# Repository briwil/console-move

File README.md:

# Console on the Ableton Move

An 8-track tape recorder with OP-1/OP-XY-style editing, up to 8 instruments (drum machines and synths, including
ones from Schwung's catalog) and step sequencers, running as an app on an Ableton Move.

- **Install:** the one-line command on [consoleforthemove.com](https://consoleforthemove.com) (needs RNBO Move Takeover on the Move)
- **Releases and notes:** [Releases](https://github.com/briwil/console-move/releases)
- **How to use it:** [move/manual/Console-on-Move-Manual.pdf](move/manual/Console-on-Move-Manual.pdf)
- **How it works / notes:** [move/MOVE-NOTES.md](move/MOVE-NOTES.md)
- **Updating the Move:** Menu, SETTINGS, SOFTWARE UPDATE (see [move/UPDATE.md](move/UPDATE.md))

| Folder | What it holds |
|---|---|
| `move/` | The Move's screen and buttons, the updater, the build script, notes and manual |
| `pi-app/` | The app itself: audio engine, sound core (C), drum machines, sequencers, Schwung support, Ableton Link |
| `tools/` | The screen designer and the stand-in modules the Move app uses |

The libraries (synths, sound core, Link...) are compiled in the cloud by GitHub Actions
(`.github/workflows/move-libs.yml`) and downloaded by the updater.

*Originally this was a Raspberry Pi recorder; its history (including the KiCad control board) is in the git log.*

## Licence and third-party work

Console is free software under the GNU General Public License v3.0 ([LICENSE](LICENSE)). It bundles drum engines, effects and Schwung modules made by other people, each under its own licence; they are listed in [THIRD-PARTY-NOTICES.md](THIRD-PARTY-NOTICES.md). Those modules belong to their authors. If you made one and want it credited differently, relicensed or removed, please open an issue on this repository and it will be dealt with promptly.

"Erica Synths", "LXR" and "LXR-02" are trademarks of Erica Synths; "Ableton" and "Move" are trademarks of Ableton AG. Console is not affiliated with or endorsed by either company.

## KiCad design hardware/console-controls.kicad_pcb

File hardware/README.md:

# Control board (rev 0.1)

The next version, split into three boards with 16 step buttons and 6 more keys, is in
[v2/](v2/README.md).

Open `console-controls.kicad_pro` in KiCad 10. The project's footprint library,
`console.pretty`, has the PGA2350 and the Kailh Choc hotswap footprints, and
`fp-lib-table` loads it automatically.

- `console-controls.kicad_pcb` is the final routed board that was ordered from
  JLCPCB (0 DRC errors).
- `console-controls.kicad_sch` is the schematic with LCSC part numbers. If you
  edited the schematic yourself in KiCad, replace this copy with yours.
- `jlcpcb-order/` holds the BOM and CPL used for assembly, which places 40
  parts on the bottom side. The hotswap sockets were out of stock, so they're
  left off and get hand-soldered.

## Pin map (PGA2350)

| Function | Pins |
|---|---|
| Key matrix rows ROW0–ROW5 | GP2–GP7 |
| Key matrix columns COL0–COL5 | GP8–GP13 |
| Encoders ENC1–ENC11, A/B | GP14/15 … GP34/35, in order |
| Spare | GP0, GP1, GP36–GP46 |
| Reserved | GP47 (PSRAM chip select) |

- **Matrix:** 6×6, COL2ROW. Each diode's cathode (the bar) faces the row.
- **Keys:** SW1–SW16 are the 4×4 grid and SW17–SW24 are the track keys.
- **Encoder pushes:** the ENC1–ENC11 push switches are also in the matrix.
- **Buttons:** SW25 is BOOT and SW26 is RESET.

## Hand assembly after the boards arrive

1. Snap off the 5 mm edge rails.
2. Solder the 24 hotswap sockets on the back.
3. Solder the 11 EC11 encoders.
4. Solder the PGA2350, using 2.54 mm headers or soldering it directly.

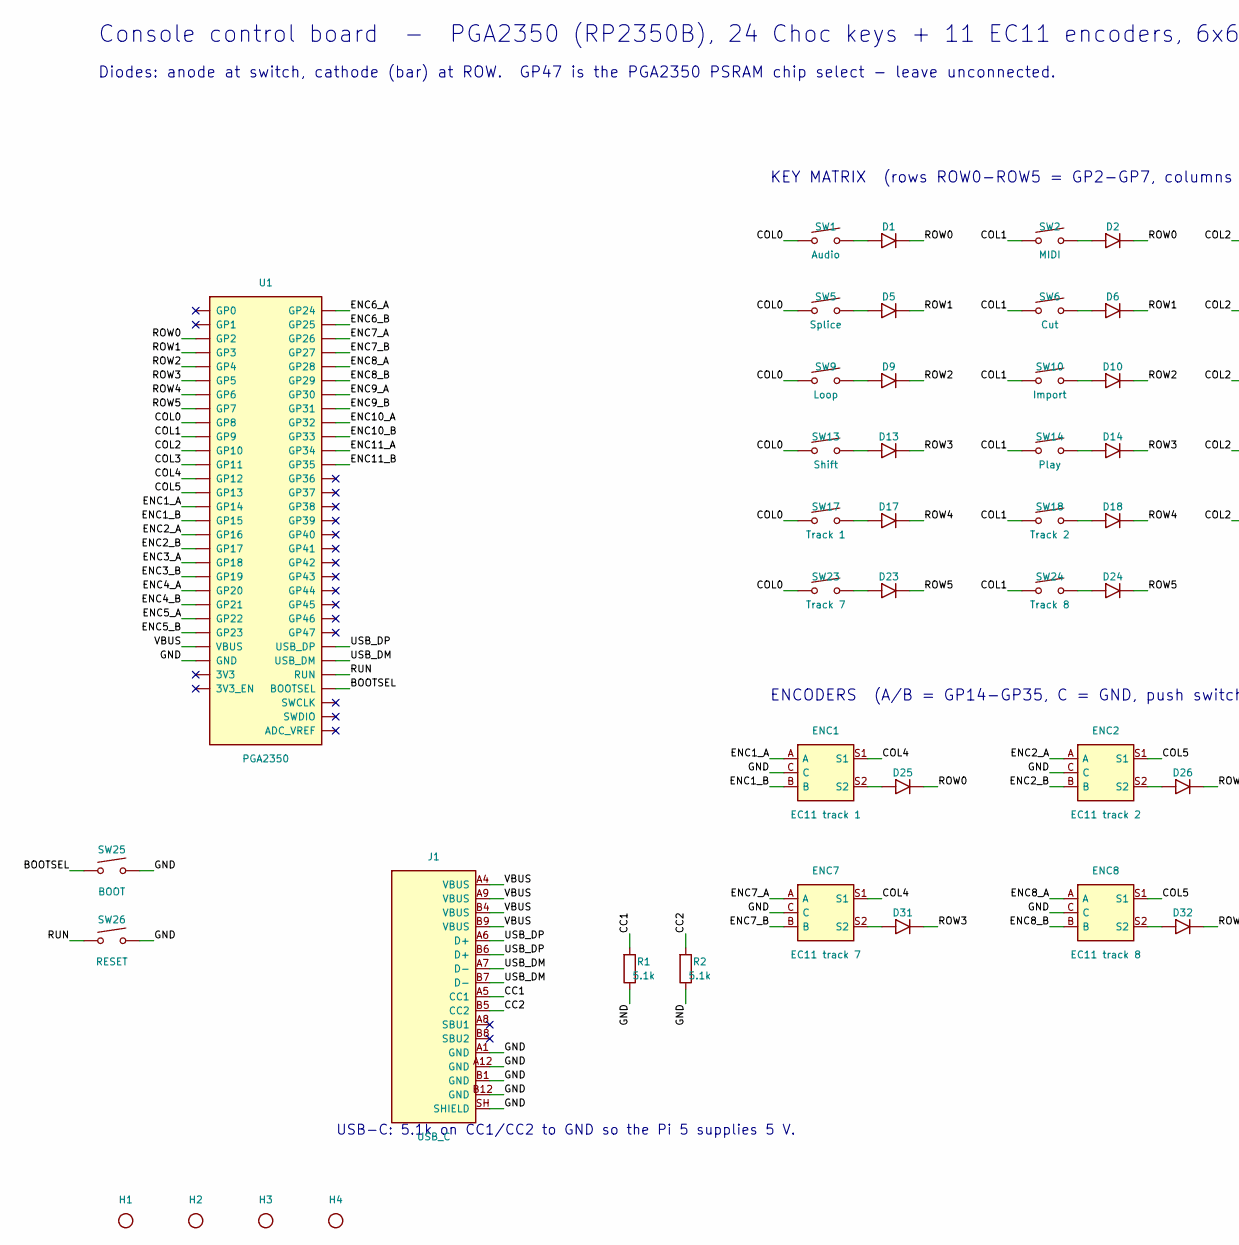
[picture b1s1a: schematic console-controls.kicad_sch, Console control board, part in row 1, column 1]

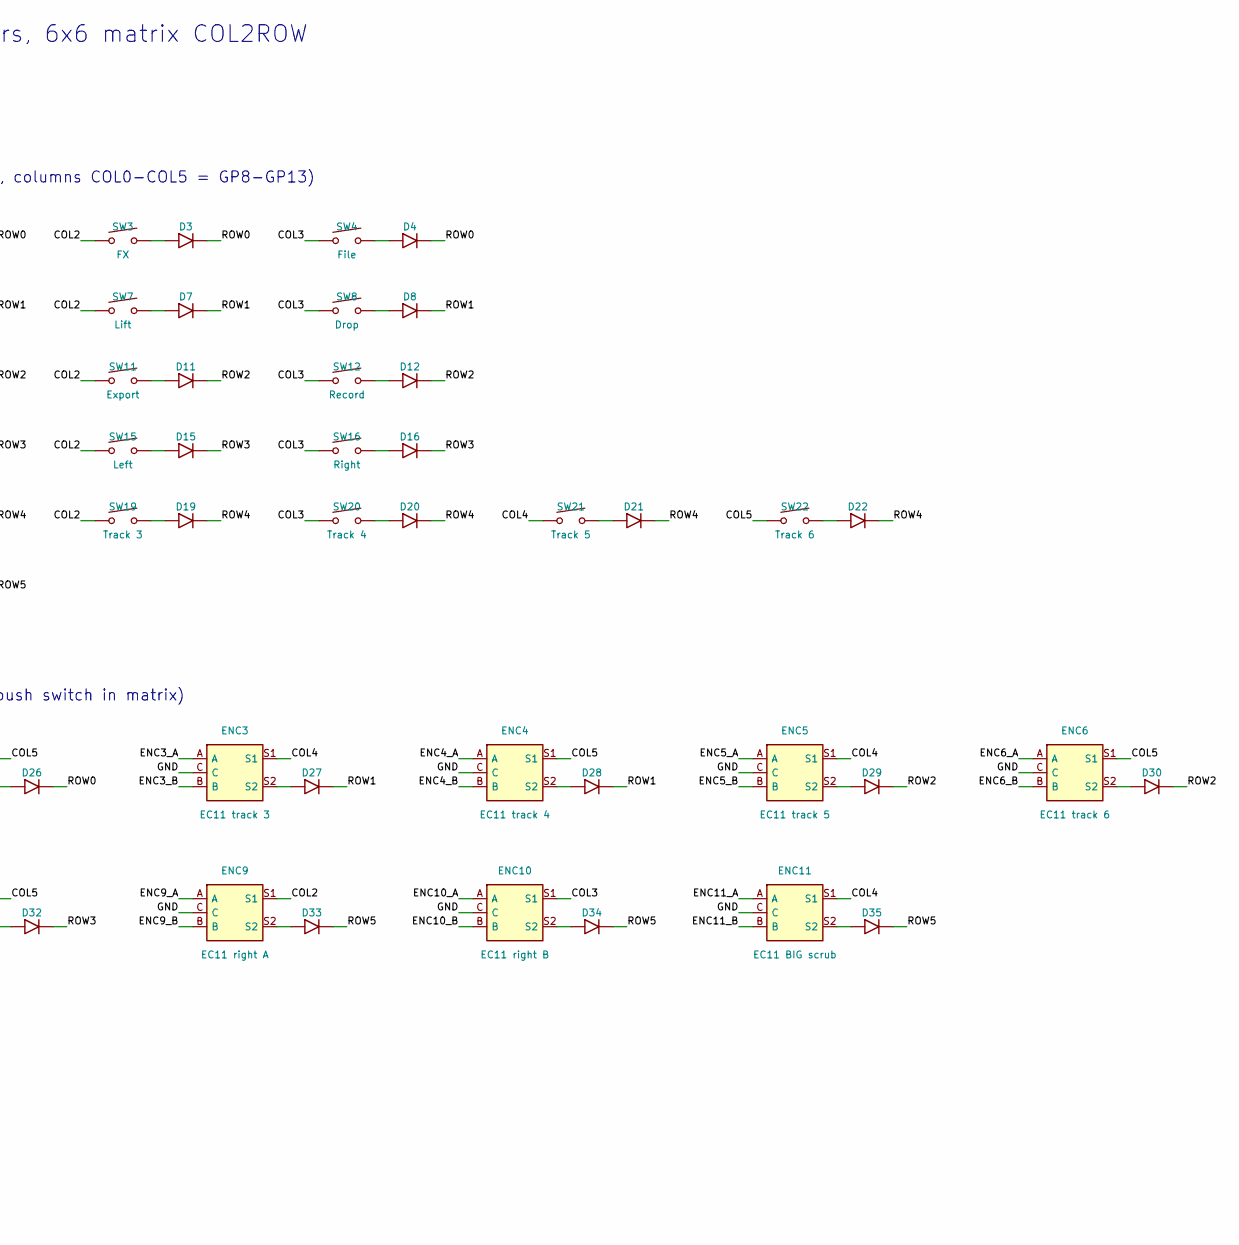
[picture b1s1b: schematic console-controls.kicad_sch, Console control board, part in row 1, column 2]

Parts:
D1, D2, D3, D4, D5, D6, D7, D8, D9, D10, D11, D12, D13, D14, D15, D16, D17, D18, D19, D20, D21, D22, D23, D24, D25, D26, D27, D28, D29, D30, D31, D32, D33, D34, D35: 1N4148W; D_SOD-123; LCSC C81598
ENC1: EC11 track 1; RotaryEncoder_Alps_EC11E-Switch_Vertical_H20mm
ENC2: EC11 track 2; RotaryEncoder_Alps_EC11E-Switch_Vertical_H20mm
ENC3: EC11 track 3; RotaryEncoder_Alps_EC11E-Switch_Vertical_H20mm
ENC4: EC11 track 4; RotaryEncoder_Alps_EC11E-Switch_Vertical_H20mm
ENC5: EC11 track 5; RotaryEncoder_Alps_EC11E-Switch_Vertical_H20mm
ENC6: EC11 track 6; RotaryEncoder_Alps_EC11E-Switch_Vertical_H20mm
ENC7: EC11 track 7; RotaryEncoder_Alps_EC11E-Switch_Vertical_H20mm
ENC8: EC11 track 8; RotaryEncoder_Alps_EC11E-Switch_Vertical_H20mm
ENC9: EC11 right A; RotaryEncoder_Alps_EC11E-Switch_Vertical_H20mm
ENC10: EC11 right B; RotaryEncoder_Alps_EC11E-Switch_Vertical_H20mm
ENC11: EC11 BIG scrub; RotaryEncoder_Alps_EC11E-Switch_Vertical_H20mm
H1, H2, H3, H4: MountingHole; MountingHole_3.2mm_M3
J1: USB_C; USB_C_Receptacle_HRO_TYPE-C-31-M-12; LCSC C165948
R1, R2: 5.1k; R_0603_1608Metric; LCSC C23186
SW1: Audio; SW_Kailh_Choc_V1_Hotswap; LCSC C5333465
SW2: MIDI; SW_Kailh_Choc_V1_Hotswap; LCSC C5333465
SW3: FX; SW_Kailh_Choc_V1_Hotswap; LCSC C5333465
SW4: File; SW_Kailh_Choc_V1_Hotswap; LCSC C5333465
SW5: Splice; SW_Kailh_Choc_V1_Hotswap; LCSC C5333465
SW6: Cut; SW_Kailh_Choc_V1_Hotswap; LCSC C5333465
SW7: Lift; SW_Kailh_Choc_V1_Hotswap; LCSC C5333465
SW8: Drop; SW_Kailh_Choc_V1_Hotswap; LCSC C5333465
SW9: Loop; SW_Kailh_Choc_V1_Hotswap; LCSC C5333465
SW10: Import; SW_Kailh_Choc_V1_Hotswap; LCSC C5333465
SW11: Export; SW_Kailh_Choc_V1_Hotswap; LCSC C5333465
SW12: Record; SW_Kailh_Choc_V1_Hotswap; LCSC C5333465
SW13: Shift; SW_Kailh_Choc_V1_Hotswap; LCSC C5333465
SW14: Play; SW_Kailh_Choc_V1_Hotswap; LCSC C5333465
SW15: Left; SW_Kailh_Choc_V1_Hotswap; LCSC C5333465
SW16: Right; SW_Kailh_Choc_V1_Hotswap; LCSC C5333465
SW17: Track 1; SW_Kailh_Choc_V1_Hotswap; LCSC C5333465
SW18: Track 2; SW_Kailh_Choc_V1_Hotswap; LCSC C5333465
SW19: Track 3; SW_Kailh_Choc_V1_Hotswap; LCSC C5333465
SW20: Track 4; SW_Kailh_Choc_V1_Hotswap; LCSC C5333465
SW21: Track 5; SW_Kailh_Choc_V1_Hotswap; LCSC C5333465
SW22: Track 6; SW_Kailh_Choc_V1_Hotswap; LCSC C5333465
SW23: Track 7; SW_Kailh_Choc_V1_Hotswap; LCSC C5333465
SW24: Track 8; SW_Kailh_Choc_V1_Hotswap; LCSC C5333465
SW25: BOOT; SW_SPST_TL3342; LCSC C2886898
SW26: RESET; SW_SPST_TL3342; LCSC C2886898
U1: PGA2350

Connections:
/BOOTSEL: SW25.1, U1.A8 (BOOTSEL)
/CC1: J1.A5 (CC1), R1.1
/CC2: J1.B5 (CC2), R2.1
/COL0: SW1.1, SW5.1, SW9.1, SW13.1, SW17.1, SW23.1, U1.E1 (GP8)
/COL1: SW2.1, SW6.1, SW10.1, SW14.1, SW18.1, SW24.1, U1.F2 (GP9)
/COL2: ENC9.S1, SW3.1, SW7.1, SW11.1, SW15.1, SW19.1, U1.F1 (GP10)
/COL3: ENC10.S1, SW4.1, SW8.1, SW12.1, SW16.1, SW20.1, U1.G2 (GP11)
/COL4: ENC1.S1, ENC3.S1, ENC5.S1, ENC7.S1, ENC11.S1, SW21.1, U1.G1 (GP12)
/COL5: ENC2.S1, ENC4.S1, ENC6.S1, ENC8.S1, SW22.1, U1.H2 (GP13)
/ENC1_A: ENC1.A, U1.H1 (GP14)
/ENC1_B: ENC1.B, U1.I2 (GP15)
/ENC2_A: ENC2.A, U1.I1 (GP16)
/ENC2_B: ENC2.B, U1.J2 (GP17)
/ENC3_A: ENC3.A, U1.J3 (GP18)
/ENC3_B: ENC3.B, U1.I3 (GP19)
/ENC4_A: ENC4.A, U1.J4 (GP20)
/ENC4_B: ENC4.B, U1.I4 (GP21)
/ENC5_A: ENC5.A, U1.J5 (GP22)
/ENC5_B: ENC5.B, U1.I5 (GP23)
/ENC6_A: ENC6.A, U1.J6 (GP24)
/ENC6_B: ENC6.B, U1.I6 (GP25)
/ENC7_A: ENC7.A, U1.J7 (GP26)
/ENC7_B: ENC7.B, U1.I7 (GP27)
/ENC8_A: ENC8.A, U1.J8 (GP28)
/ENC8_B: ENC8.B, U1.I8 (GP29)
/ENC9_A: ENC9.A, U1.J9 (GP30)
/ENC9_B: ENC9.B, U1.I9 (GP31)
/ENC10_A: ENC10.A, U1.I10 (GP32)
/ENC10_B: ENC10.B, U1.H9 (GP33)
/ENC11_A: ENC11.A, U1.H10 (GP34)
/ENC11_B: ENC11.B, U1.G9 (GP35)
/GND: ENC1.C, ENC2.C, ENC3.C, ENC4.C, ENC5.C, ENC6.C, ENC7.C, ENC8.C, ENC9.C, ENC10.C, ENC11.C, J1.A1 (GND), J1.A12 (GND), J1.B1 (GND), J1.B12 (GND), J1.SH (SHIELD), R1.2, R2.2, SW25.2, SW26.2, U1.A1 (GND), U1.A10 (GND), U1.B2 (GND), U1.B9 (GND), U1.J1 (GND), U1.J10 (GND)
/ROW0: D1.1 (K), D2.1 (K), D3.1 (K), D4.1 (K), D25.1 (K), D26.1 (K), U1.B1 (GP2)
/ROW1: D5.1 (K), D6.1 (K), D7.1 (K), D8.1 (K), D27.1 (K), D28.1 (K), U1.C2 (GP3)
/ROW2: D9.1 (K), D10.1 (K), D11.1 (K), D12.1 (K), D29.1 (K), D30.1 (K), U1.C1 (GP4)
/ROW3: D13.1 (K), D14.1 (K), D15.1 (K), D16.1 (K), D31.1 (K), D32.1 (K), U1.D2 (GP5)
/ROW4: D17.1 (K), D18.1 (K), D19.1 (K), D20.1 (K), D21.1 (K), D22.1 (K), U1.D1 (GP6)
/ROW5: D23.1 (K), D24.1 (K), D33.1 (K), D34.1 (K), D35.1 (K), U1.E2 (GP7)
/RUN: SW26.1, U1.A5 (RUN)
/USB_DM: J1.A7 (D-), J1.B7 (D-), U1.A7 (USB_DM)
/USB_DP: J1.A6 (D+), J1.B6 (D+), U1.A6 (USB_DP)
/VBUS: J1.A4 (VBUS), J1.A9 (VBUS), J1.B4 (VBUS), J1.B9 (VBUS), U1.A3 (VBUS)
unnamed: D1.2 (A), SW1.2
unnamed: D2.2 (A), SW2.2
unnamed: D3.2 (A), SW3.2
unnamed: D4.2 (A), SW4.2
unnamed: D5.2 (A), SW5.2
unnamed: D6.2 (A), SW6.2
unnamed: D7.2 (A), SW7.2
unnamed: D8.2 (A), SW8.2
unnamed: D9.2 (A), SW9.2
unnamed: D10.2 (A), SW10.2
unnamed: D11.2 (A), SW11.2
unnamed: D12.2 (A), SW12.2
unnamed: D13.2 (A), SW13.2
unnamed: D14.2 (A), SW14.2
unnamed: D15.2 (A), SW15.2
unnamed: D16.2 (A), SW16.2
unnamed: D17.2 (A), SW17.2
unnamed: D18.2 (A), SW18.2
unnamed: D19.2 (A), SW19.2
unnamed: D20.2 (A), SW20.2
unnamed: D21.2 (A), SW21.2
unnamed: D22.2 (A), SW22.2
unnamed: D23.2 (A), SW23.2
unnamed: D24.2 (A), SW24.2
unnamed: D25.2 (A), ENC1.S2
unnamed: D26.2 (A), ENC2.S2
unnamed: D27.2 (A), ENC3.S2
unnamed: D28.2 (A), ENC4.S2
unnamed: D29.2 (A), ENC5.S2
unnamed: D30.2 (A), ENC6.S2
unnamed: D31.2 (A), ENC7.S2
unnamed: D32.2 (A), ENC8.S2
unnamed: D33.2 (A), ENC9.S2
unnamed: D34.2 (A), ENC10.S2
unnamed: D35.2 (A), ENC11.S2

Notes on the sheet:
Console control board - PGA2350 (RP2350B), 24 Choc keys + 11 EC11 encoders, 6x6 matrix COL2ROW
Diodes: anode at switch, cathode (bar) at ROW. GP47 is the PGA2350 PSRAM chip select - leave unconnected.
USB-C: 5.1k on CC1/CC2 to GND so the Pi 5 supplies 5 V.
KEY MATRIX (rows ROW0-ROW5 = GP2-GP7, columns COL0-COL5 = GP8-GP13)
ENCODERS (A/B = GP14-GP35, C = GND, push switch in matrix)

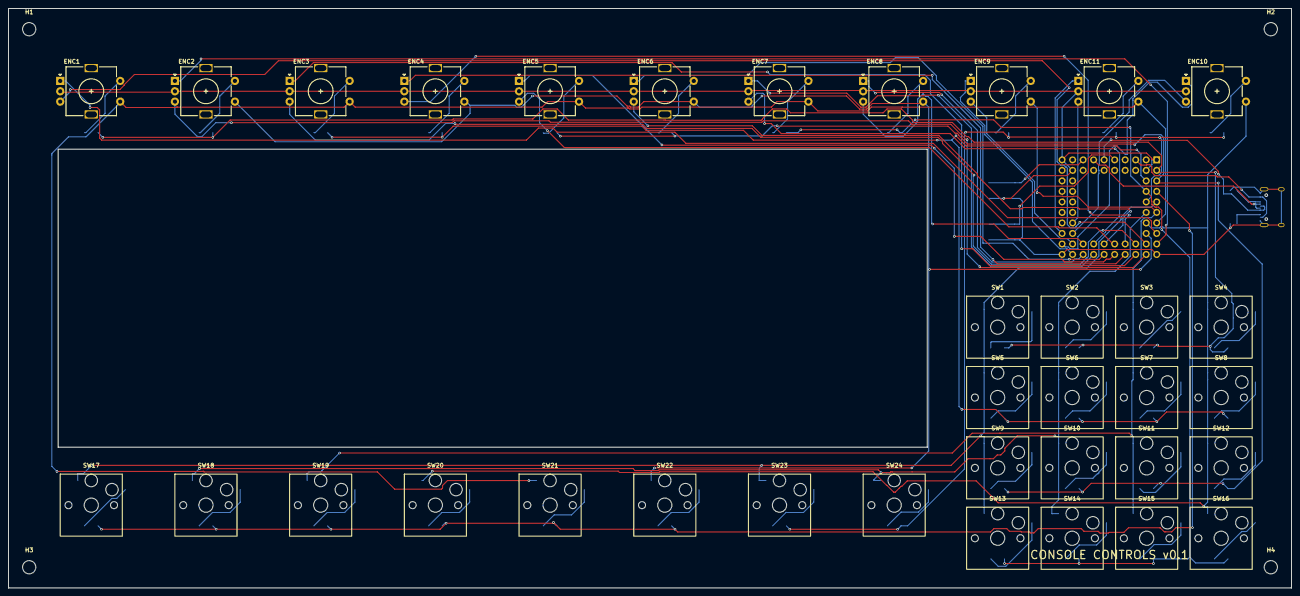
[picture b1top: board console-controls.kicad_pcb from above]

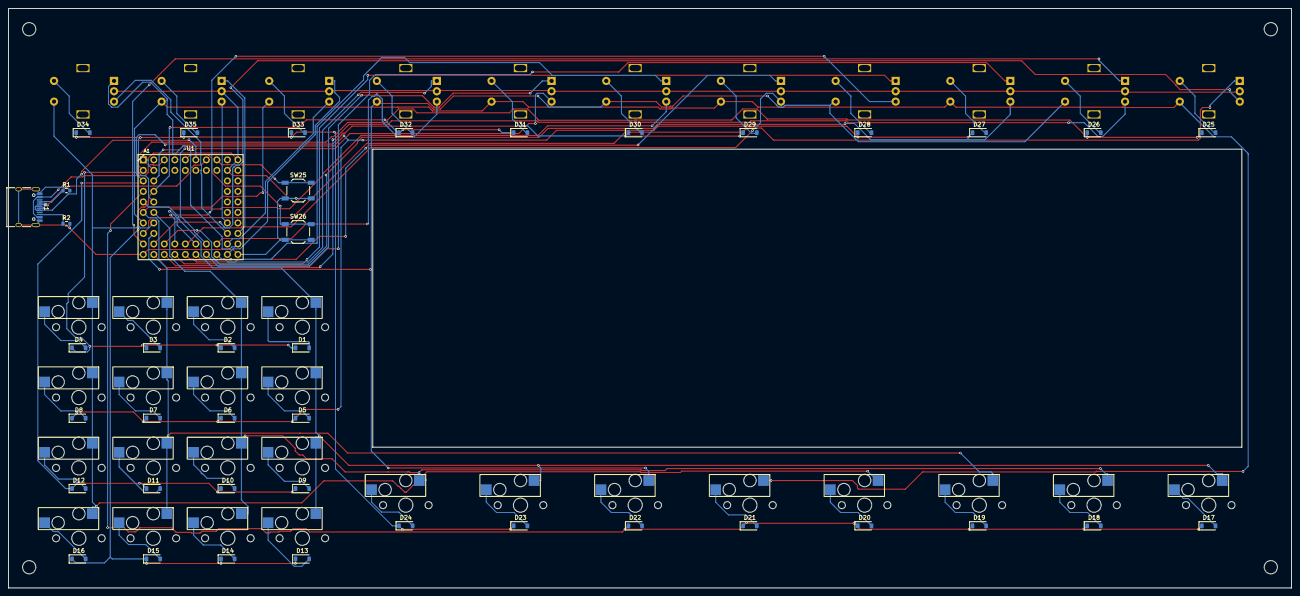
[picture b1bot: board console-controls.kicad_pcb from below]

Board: 2 copper layers, 310.0 x 140.0 mm, 80 parts (41 on the bottom side), 77 nets.

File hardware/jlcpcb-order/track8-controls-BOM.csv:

Comment,Designator,Footprint,LCSC Part #
1N4148W,"D1,D2,D3,D4,D5,D6,D7,D8,D9,D10,D11,D12,D13,D14,D15,D16,D17,D18,D19,D20,D21,D22,D23,D24,D25,D26,D27,D28,D29,D30,D31,D32,D33,D34,D35",D_SOD-123,C81598
TYPE-C-31-M-12,J1,USB_C_Receptacle_HRO_TYPE-C-31-M-12,C165948
5.1k,"R1,R2",R_0603_1608Metric,C23186
TL3342F160QG,"SW25,SW26",SW_SPST_TL3342,C2886898

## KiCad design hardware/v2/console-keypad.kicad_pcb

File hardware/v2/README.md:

# Control boards v0.2 (three boards)

The v0.1 one-piece board split into three smaller boards, joined by ribbon cables, plus 16 step
buttons and 6 new keys. The microcontroller (PGA2350) stays on the keypad board; the other two
boards are only switches, diodes and a socket.

| Board | Size | What's on it | Made by |
|---|---|---|---|
| `console-keypad.kicad_pcb` | 87.5 × 111.5 mm | the 4×4 keys, PGA2350, USB-C, BOOT and RESET, 3 cable sockets | JLCPCB fits the diodes, USB-C, resistors and buttons; you solder the rest |
| `console-keys.kicad_pcb` | 241.5 × 72.5 mm | 8 track keys, 6 new keys, 16 step buttons, 30 diodes, 1 cable socket | bare board, you solder everything |
| `console-knobs.kicad_pcb` | 258 × 35 mm | 11 knobs (with pushes), 11 diodes, 2 cable sockets | bare board, you solder everything |

The boards are made by `make_boards.py` (`python3 make_boards.py --route` places the parts, routes
them with Freerouting and writes the three `.kicad_pcb` files). Open any of them in KiCad 10.
There's no schematic for v0.2: the wiring is in `make_boards.py` and below. Routing used
Freerouting 1.6.5 built from source (with its two `== ""` string comparisons fixed so it runs on
Java 21; set `FREEROUTING_CP` to its classes folder). `route/` keeps each board's `.dsn` and the
routed `.ses`.

**Not ordered yet:** the boards still need KiCad's own design rule check and the Gerber files
made in KiCad before ordering.

## Cables

Three ribbon cables with IDC plugs. Each one goes **pin 1 to pin 1** (an ordinary straight ribbon
cable with the plugs crimped the same way round; the red stripe is pin 1). The sockets are
shrouded box headers, so the plugs only go in one way.

| Cable | From (keypad board) | To | Pins |
|---|---|---|---|
| Knobs 1-6 | J2 | knob board J1 | 20 (2×10) |
| Knobs 7-11 | J3 | knob board J2 | 20 (2×10) |
| Keys | J4 | keys board J1 | 16 (2×8) |

All the sockets are on the back of the boards.

## Pin map (PGA2350)

| Function | Pins |
|---|---|
| Key matrix rows ROW0-ROW5 | GP2-GP7 (shared by all three boards) |
| Keypad columns COL0-COL3 | GP8-GP11 |
| Knob pushes COL4 (knobs 1-6), COL5 (knobs 7-11) | GP12, GP13 |
| Knobs 1-11 A/B, left to right | GP14/15 … GP34/35 |
| Keys board columns COL6-COL10 | GP36-GP40 |
| Spare | GP0, GP1, GP41-GP46 |

Matrix: 6 rows × 11 columns, columns to anodes: switch from the column to the diode's anode, the
diode's cathode (the band) to the row.

| Column | Rows 0-5 |
|---|---|
| COL0-COL3 | keys 1-16 (the 4×4 grid, row by row) |
| COL4 | knob pushes 1-6 |
| COL5 | knob pushes 7-11 (rows 0-4) |
| COL6 | steps 1-6 |
| COL7 | steps 7-12 |
| COL8 | steps 13-16 (rows 0-3), track keys 7-8 (rows 4-5) |
| COL9 | track keys 1-6 |
| COL10 | new keys 1-6 (the top row, left to right) |

The firmware (`../../firmware/code.py`) has both boards' maps: set `BOARD = 2` for these.

### Cable pins

Knobs 1-6 (2×10): 1 GND, 2 COL4, 3-8 ROW0-ROW5, 9/10 knob 1 A/B, 11/12 knob 2 A/B … 19/20 knob 6 A/B.

Knobs 7-11 (2×10): 1 GND, 2 COL5, 3-7 ROW0-ROW4, 8 GND, 9/10 knob 7 A/B … 17/18 knob 11 A/B, 19-20 GND.

Keys (2×8): 1-6 ROW0-ROW5, 7-11 COL6-COL10, 12-16 GND (not used on the keys board).

## Parts to buy (besides what JLCPCB fits)

- 1 × PGA2350 (or reuse the v0.1 one)
- 14 × Kailh Choc V1 switches and 14 hotswap sockets (CPG135001S30): 8 track keys + 6 new keys
- 16 × Choc V1 switches and sockets for the keypad (or reuse the v0.1 ones)
- 16 × 6×6 mm through-hole tactile switches, 4 pins (the height to suit the case)
- 41 × 1N4148 diodes, through-hole (DO-35)
- 11 × EC11 encoders with push switch (the ones you have)
- 4 × 2×10 shrouded box headers, 2.54 mm (IDC, vertical)
- 2 × 2×8 shrouded box headers, 2.54 mm
- 2 × 20-pin and 1 × 16-pin IDC ribbon cables, 2.54 mm, plug at each end, the same way round
  (16-pin to 16-pin, not the 10-to-16 Eurorack power kind)
- 16 × M3 screws and standoffs (4 + 6 + 6)

## Hand assembly

Keys board and knob board: diodes first (the band goes on the side marked on the board), then the
hotswap sockets (back), tactile switches and encoders (front), then the box header (back, notch as
drawn). Keypad board: the 16 hotswap sockets, the PGA2350 and the three box headers.

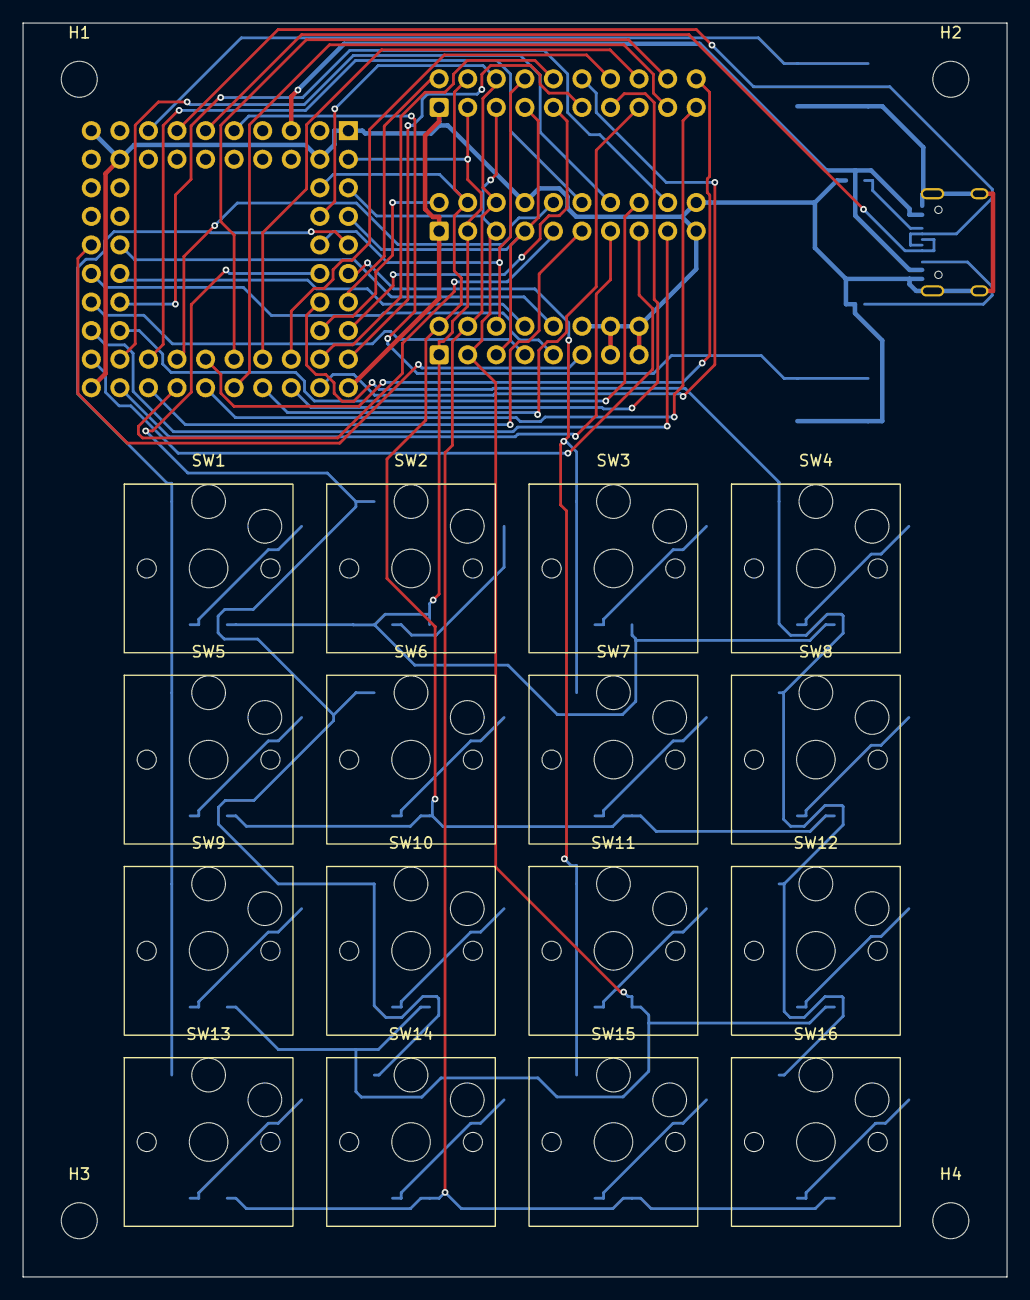
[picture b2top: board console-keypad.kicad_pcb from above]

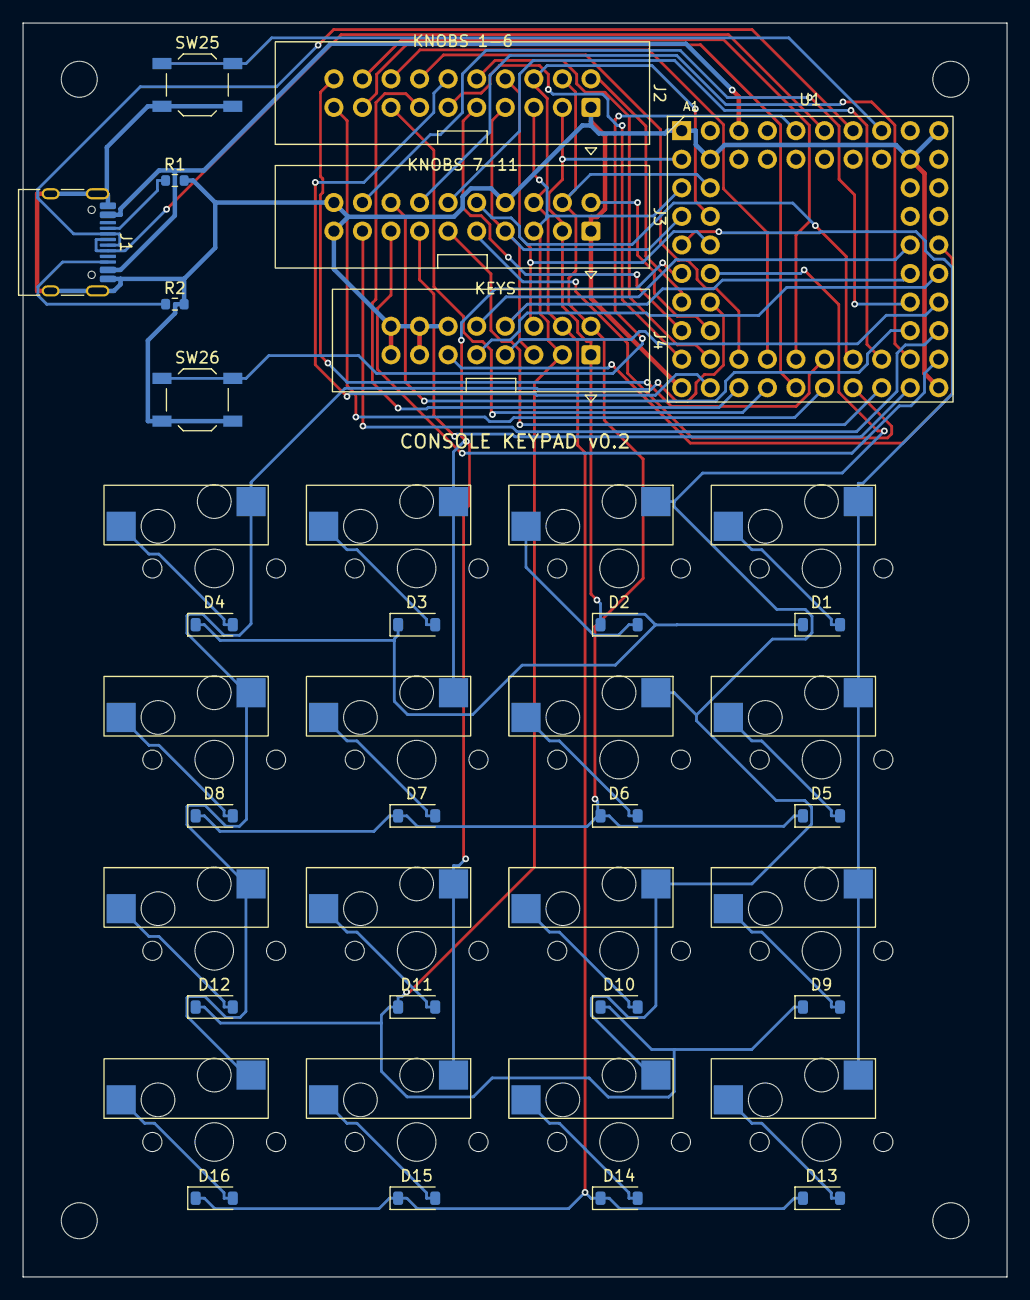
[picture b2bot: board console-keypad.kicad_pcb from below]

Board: 2 copper layers, 87.5 x 111.5 mm, 45 parts (25 on the bottom side), 63 nets.

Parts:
D1, D2, D3, D4, D5, D6, D7, D8, D9, D10, D11, D12, D13, D14, D15, D16: 1N4148W; D_SOD-123
H1, H2, H3, H4: M3; MountingHole_3.2mm_M3
J1: USB-C; USB_C_Receptacle_HRO_TYPE-C-31-M-12
J2, J3: IDC 2x10; IDC-Header_2x10_P2.54mm_Vertical
J4: IDC 2x8; IDC-Header_2x08_P2.54mm_Vertical
R1, R2: 5.1k; R_0603_1608Metric
SW1: Key 1; SW_Kailh_Choc_V1_Hotswap
SW2: Key 2; SW_Kailh_Choc_V1_Hotswap
SW3: Key 3; SW_Kailh_Choc_V1_Hotswap
SW4: Key 4; SW_Kailh_Choc_V1_Hotswap
SW5: Key 5; SW_Kailh_Choc_V1_Hotswap
SW6: Key 6; SW_Kailh_Choc_V1_Hotswap
SW7: Key 7; SW_Kailh_Choc_V1_Hotswap
SW8: Key 8; SW_Kailh_Choc_V1_Hotswap
SW9: Key 9; SW_Kailh_Choc_V1_Hotswap
SW10: Key 10; SW_Kailh_Choc_V1_Hotswap
SW11: Key 11; SW_Kailh_Choc_V1_Hotswap
SW12: Key 12; SW_Kailh_Choc_V1_Hotswap
SW13: Key 13; SW_Kailh_Choc_V1_Hotswap
SW14: Key 14; SW_Kailh_Choc_V1_Hotswap
SW15: Key 15; SW_Kailh_Choc_V1_Hotswap
SW16: Key 16; SW_Kailh_Choc_V1_Hotswap
SW25: BOOT; SW_SPST_TL3342
SW26: RESET; SW_SPST_TL3342
U1: PGA2350

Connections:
BOOTSEL: SW25.1, U1.A8
CC1: J1.A5, R1.1
CC2: J1.B5, R2.1
COL0: SW1.1, SW5.1, SW9.1, SW13.1, U1.E1
COL1: SW2.1, SW6.1, SW10.1, SW14.1, U1.F2
COL2: SW3.1, SW7.1, SW11.1, SW15.1, U1.F1
COL3: SW4.1, SW8.1, SW12.1, SW16.1, U1.G2
COL4: J2.2, U1.G1
COL5: J3.2, U1.H2
COL6: J4.7, U1.G10
COL7: J4.8, U1.F9
COL8: J4.9, U1.F10
COL9: J4.10, U1.E9
COL10: J4.11, U1.E10
D1_A: D1.2, SW1.2
D2_A: D2.2, SW2.2
D3_A: D3.2, SW3.2
D4_A: D4.2, SW4.2
D5_A: D5.2, SW5.2
D6_A: D6.2, SW6.2
D7_A: D7.2, SW7.2
D8_A: D8.2, SW8.2
D9_A: D9.2, SW9.2
D10_A: D10.2, SW10.2
D11_A: D11.2, SW11.2
D12_A: D12.2, SW12.2
D13_A: D13.2, SW13.2
D14_A: D14.2, SW14.2
D15_A: D15.2, SW15.2
D16_A: D16.2, SW16.2
GND: J1.A1, J1.A12, J1.B1, J1.B12, J1.SH, J2.1, J3.1, J3.8, J3.19, J3.20, J4.12, J4.13, J4.14, J4.15, J4.16, R1.2, R2.2, SW25.2, SW26.2, U1.A1, U1.A10, U1.B2, U1.B9, U1.J1, U1.J10
KNOB1_A: J2.9, U1.H1
KNOB1_B: J2.10, U1.I2
KNOB2_A: J2.11, U1.I1
KNOB2_B: J2.12, U1.J2
KNOB3_A: J2.13, U1.J3
KNOB3_B: J2.14, U1.I3
KNOB4_A: J2.15, U1.J4
KNOB4_B: J2.16, U1.I4
KNOB5_A: J2.17, U1.J5
KNOB5_B: J2.18, U1.I5
KNOB6_A: J2.19, U1.J6
KNOB6_B: J2.20, U1.I6
KNOB7_A: J3.9, U1.J7
KNOB7_B: J3.10, U1.I7
KNOB8_A: J3.11, U1.J8
KNOB8_B: J3.12, U1.I8
KNOB9_A: J3.13, U1.J9
KNOB9_B: J3.14, U1.I9
KNOB10_A: J3.15, U1.I10
KNOB10_B: J3.16, U1.H9
KNOB11_A: J3.17, U1.H10
KNOB11_B: J3.18, U1.G9
ROW0: D1.1, D2.1, D3.1, D4.1, J2.3, J3.3, J4.1, U1.B1
ROW1: D5.1, D6.1, D7.1, D8.1, J2.4, J3.4, J4.2, U1.C2
ROW2: D9.1, D10.1, D11.1, D12.1, J2.5, J3.5, J4.3, U1.C1
ROW3: D13.1, D14.1, D15.1, D16.1, J2.6, J3.6, J4.4, U1.D2
ROW4: J2.7, J3.7, J4.5, U1.D1
ROW5: J2.8, J4.6, U1.E2
RUN: SW26.1, U1.A5
USB_DM: J1.A7, J1.B7, U1.A7
USB_DP: J1.A6, J1.B6, U1.A6
VBUS: J1.A4, J1.A9, J1.B4, J1.B9, U1.A3

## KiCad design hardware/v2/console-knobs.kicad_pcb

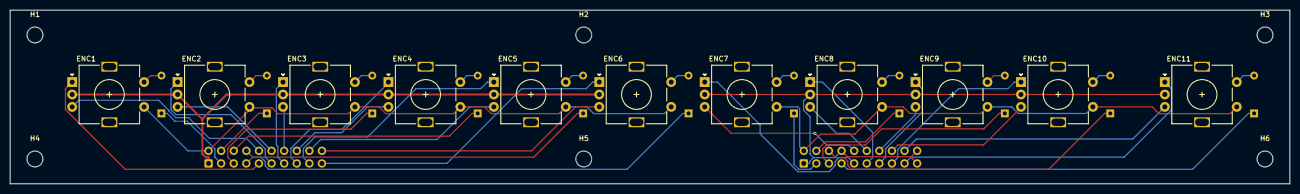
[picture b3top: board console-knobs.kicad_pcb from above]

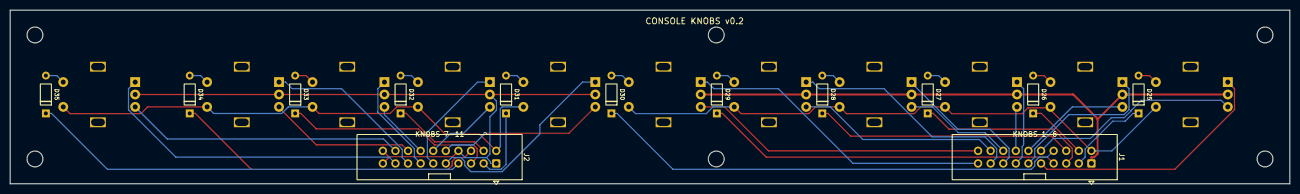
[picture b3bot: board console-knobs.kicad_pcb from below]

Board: 2 copper layers, 258.0 x 35.0 mm, 30 parts (13 on the bottom side), 48 nets.

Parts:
D25, D26, D27, D28, D29, D30, D31, D32, D33, D34, D35: 1N4148; D_DO-35_SOD27_P7.62mm_Horizontal
ENC1: Knob 1; RotaryEncoder_Alps_EC11E-Switch_Vertical_H20mm
ENC2: Knob 2; RotaryEncoder_Alps_EC11E-Switch_Vertical_H20mm
ENC3: Knob 3; RotaryEncoder_Alps_EC11E-Switch_Vertical_H20mm
ENC4: Knob 4; RotaryEncoder_Alps_EC11E-Switch_Vertical_H20mm
ENC5: Knob 5; RotaryEncoder_Alps_EC11E-Switch_Vertical_H20mm
ENC6: Knob 6; RotaryEncoder_Alps_EC11E-Switch_Vertical_H20mm
ENC7: Knob 7; RotaryEncoder_Alps_EC11E-Switch_Vertical_H20mm
ENC8: Knob 8; RotaryEncoder_Alps_EC11E-Switch_Vertical_H20mm
ENC9: Knob 9; RotaryEncoder_Alps_EC11E-Switch_Vertical_H20mm
ENC10: Knob 10; RotaryEncoder_Alps_EC11E-Switch_Vertical_H20mm
ENC11: Knob 11; RotaryEncoder_Alps_EC11E-Switch_Vertical_H20mm
H1, H2, H3, H4, H5, H6: M3; MountingHole_3.2mm_M3
J1, J2: IDC 2x10; IDC-Header_2x10_P2.54mm_Vertical

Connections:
COL4: ENC1.S1, ENC2.S1, ENC3.S1, ENC4.S1, ENC5.S1, ENC6.S1, J1.2
COL5_B: ENC7.S1, ENC8.S1, ENC9.S1, ENC10.S1, ENC11.S1, J2.2
D25_A: D25.2, ENC1.S2
D26_A: D26.2, ENC2.S2
D27_A: D27.2, ENC3.S2
D28_A: D28.2, ENC4.S2
D29_A: D29.2, ENC5.S2
D30_A: D30.2, ENC6.S2
D31_A: D31.2, ENC7.S2
D32_A: D32.2, ENC8.S2
D33_A: D33.2, ENC9.S2
D34_A: D34.2, ENC10.S2
D35_A: D35.2, ENC11.S2
GND: ENC1.C, ENC2.C, ENC3.C, ENC4.C, ENC5.C, ENC6.C, J1.1
GND_B: ENC7.C, ENC8.C, ENC9.C, ENC10.C, ENC11.C, J2.1, J2.8, J2.19, J2.20
KNOB1_A: ENC1.A, J1.9
KNOB1_B: ENC1.B, J1.10
KNOB2_A: ENC2.A, J1.11
KNOB2_B: ENC2.B, J1.12
KNOB3_A: ENC3.A, J1.13
KNOB3_B: ENC3.B, J1.14
KNOB4_A: ENC4.A, J1.15
KNOB4_B: ENC4.B, J1.16
KNOB5_A: ENC5.A, J1.17
KNOB5_B: ENC5.B, J1.18
KNOB6_A: ENC6.A, J1.19
KNOB6_B: ENC6.B, J1.20
KNOB7_A: ENC7.A, J2.9
KNOB7_B: ENC7.B, J2.10
KNOB8_A: ENC8.A, J2.11
KNOB8_B: ENC8.B, J2.12
KNOB9_A: ENC9.A, J2.13
KNOB9_B: ENC9.B, J2.14
KNOB10_A: ENC10.A, J2.15
KNOB10_B: ENC10.B, J2.16
KNOB11_A: ENC11.A, J2.17
KNOB11_B: ENC11.B, J2.18
ROW0: D25.1, J1.3
ROW0_B: D31.1, J2.3
ROW1: D26.1, J1.4
ROW1_B: D32.1, J2.4
ROW2: D27.1, J1.5
ROW2_B: D33.1, J2.5
ROW3: D28.1, J1.6
ROW3_B: D34.1, J2.6
ROW4: D29.1, J1.7
ROW4_B: D35.1, J2.7
ROW5: D30.1, J1.8

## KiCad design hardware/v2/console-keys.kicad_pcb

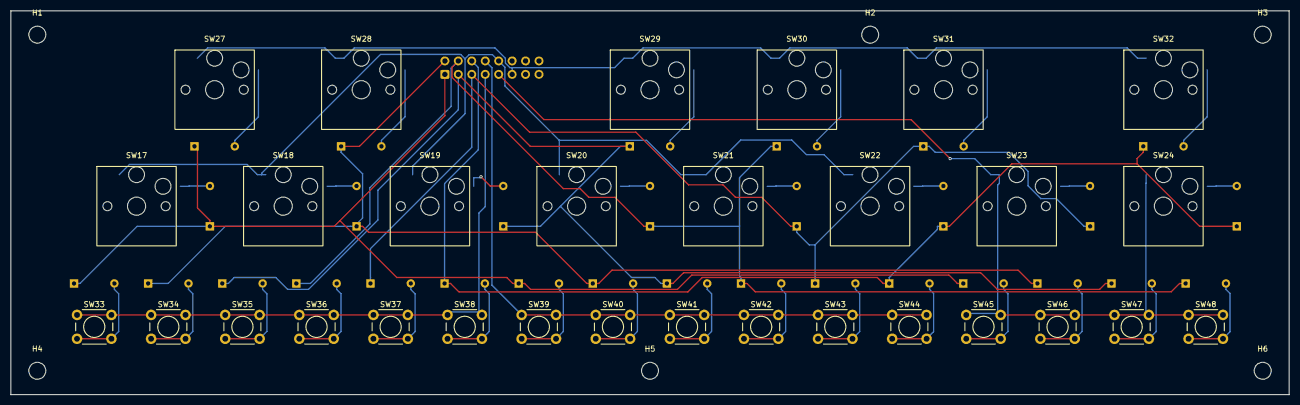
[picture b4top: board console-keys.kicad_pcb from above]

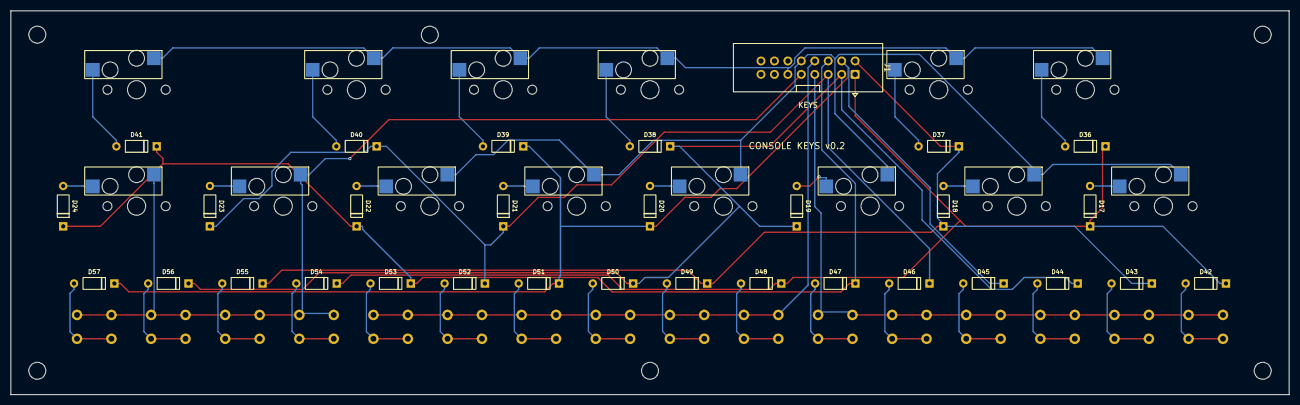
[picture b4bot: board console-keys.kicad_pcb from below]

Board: 2 copper layers, 241.5 x 72.5 mm, 67 parts (31 on the bottom side), 41 nets.

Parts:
D17, D18, D19, D20, D21, D22, D23, D24, D36, D37, D38, D39, D40, D41, D42, D43, D44, D45, D46, D47, D48, D49, D50, D51, D52, D53, D54, D55, D56, D57: 1N4148; D_DO-35_SOD27_P7.62mm_Horizontal
H1, H2, H3, H4, H5, H6: M3; MountingHole_3.2mm_M3
J1: IDC 2x8; IDC-Header_2x08_P2.54mm_Vertical
SW17: Track 1; SW_Kailh_Choc_V1_Hotswap
SW18: Track 2; SW_Kailh_Choc_V1_Hotswap
SW19: Track 3; SW_Kailh_Choc_V1_Hotswap
SW20: Track 4; SW_Kailh_Choc_V1_Hotswap
SW21: Track 5; SW_Kailh_Choc_V1_Hotswap
SW22: Track 6; SW_Kailh_Choc_V1_Hotswap
SW23: Track 7; SW_Kailh_Choc_V1_Hotswap
SW24: Track 8; SW_Kailh_Choc_V1_Hotswap
SW27: New key 1; SW_Kailh_Choc_V1_Hotswap
SW28: New key 2; SW_Kailh_Choc_V1_Hotswap
SW29: New key 3; SW_Kailh_Choc_V1_Hotswap
SW30: New key 4; SW_Kailh_Choc_V1_Hotswap
SW31: New key 5; SW_Kailh_Choc_V1_Hotswap
SW32: New key 6; SW_Kailh_Choc_V1_Hotswap
SW33: Step 1; SW_PUSH_6mm
SW34: Step 2; SW_PUSH_6mm
SW35: Step 3; SW_PUSH_6mm
SW36: Step 4; SW_PUSH_6mm
SW37: Step 5; SW_PUSH_6mm
SW38: Step 6; SW_PUSH_6mm
SW39: Step 7; SW_PUSH_6mm
SW40: Step 8; SW_PUSH_6mm
SW41: Step 9; SW_PUSH_6mm
SW42: Step 10; SW_PUSH_6mm
SW43: Step 11; SW_PUSH_6mm
SW44: Step 12; SW_PUSH_6mm
SW45: Step 13; SW_PUSH_6mm
SW46: Step 14; SW_PUSH_6mm
SW47: Step 15; SW_PUSH_6mm
SW48: Step 16; SW_PUSH_6mm

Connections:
COL6: J1.7, SW33.1, SW34.1, SW35.1, SW36.1, SW37.1, SW38.1
COL7: J1.8, SW39.1, SW40.1, SW41.1, SW42.1, SW43.1, SW44.1
COL8: J1.9, SW23.1, SW24.1, SW45.1, SW46.1, SW47.1, SW48.1
COL9: J1.10, SW17.1, SW18.1, SW19.1, SW20.1, SW21.1, SW22.1
COL10: J1.11, SW27.1, SW28.1, SW29.1, SW30.1, SW31.1, SW32.1
D17_A: D17.2, SW17.2
D18_A: D18.2, SW18.2
D19_A: D19.2, SW19.2
D20_A: D20.2, SW20.2
D21_A: D21.2, SW21.2
D22_A: D22.2, SW22.2
D23_A: D23.2, SW23.2
D24_A: D24.2, SW24.2
D36_A: D36.2, SW27.2
D37_A: D37.2, SW28.2
D38_A: D38.2, SW29.2
D39_A: D39.2, SW30.2
D40_A: D40.2, SW31.2
D41_A: D41.2, SW32.2
D42_A: D42.2, SW33.2
D43_A: D43.2, SW34.2
D44_A: D44.2, SW35.2
D45_A: D45.2, SW36.2
D46_A: D46.2, SW37.2
D47_A: D47.2, SW38.2
D48_A: D48.2, SW39.2
D49_A: D49.2, SW40.2
D50_A: D50.2, SW41.2
D51_A: D51.2, SW42.2
D52_A: D52.2, SW43.2
D53_A: D53.2, SW44.2
D54_A: D54.2, SW45.2
D55_A: D55.2, SW46.2
D56_A: D56.2, SW47.2
D57_A: D57.2, SW48.2
ROW0: D17.1, D36.1, D42.1, D48.1, D54.1, J1.1
ROW1: D18.1, D37.1, D43.1, D49.1, D55.1, J1.2
ROW2: D19.1, D38.1, D44.1, D50.1, D56.1, J1.3
ROW3: D20.1, D39.1, D45.1, D51.1, D57.1, J1.4
ROW4: D21.1, D23.1, D40.1, D46.1, D52.1, J1.5
ROW5: D22.1, D24.1, D41.1, D47.1, D53.1, J1.6

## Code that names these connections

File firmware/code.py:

# Console control board firmware (CircuitPython 10 on the Pimoroni PGA2350).
#
# Reads the keys, the 11 knobs and the 11 knob pushes, and sends them to the
# Pi as USB MIDI on channel 16:
#   keys SW1-SW24        note 0-23     (note on when pressed, note off when let go)
#   new keys 1-6         note 24-29    (v0.2 boards only: the top row of the long board)
#   knob pushes 1-11     note 32-42    (by position, left to right)
#   step buttons 1-16    note 48-63    (v0.2 boards only)
#   knob turns 1-11      CC 1-11, relative: 64 + clicks (65 = one click right, 63 = one left)
#
# BOARD below says which control board this runs on: 1 = the one-piece v0.1 board,
# 2 = the three v0.2 boards (hardware/v2). The pin maps are in hardware/README.md and hardware/v2/README.md.
import time

import keypad
import microcontroller
import usb_midi

CHANNEL = 15                      # MIDI channel 16 (counted from 0)
DIVISOR = 4                       # encoder steps per click; change to 2 if one click moves two steps
BOARD = 1                         # 1 = v0.1 board, 2 = the v0.2 boards


def pin(n):
    return getattr(microcontroller.pin, "GPIO%d" % n)


# ---------------------------------------------------------------- keys (6x6 matrix, diodes column to row)

ROW_PINS = [pin(n) for n in range(2, 8)]      # ROW0-ROW5 = GP2-GP7
if BOARD == 1:
    COL_PINS = [pin(n) for n in range(8, 14)]                               # COL0-COL5 = GP8-GP13
else:
    COL_PINS = [pin(n) for n in range(8, 14)] + [pin(n) for n in range(36, 41)]   # + COL6-COL10 = GP36-GP40
matrix = keypad.KeyMatrix(row_pins=ROW_PINS, column_pins=COL_PINS, columns_to_anodes=True, interval=0.005)

# matrix position (row, column) -> MIDI note
NOTE = {}
for n in range(1, 17):                         # SW1-SW16: the 4x4 grid, rows 0-3, columns 0-3
    NOTE[((n - 1) // 4, (n - 1) % 4)] = n - 1
if BOARD == 1:
    for i in range(6):                         # SW17-SW22: track keys 1-6, row 4
        NOTE[(4, i)] = 16 + i
    NOTE[(5, 0)] = 22                          # SW23: track key 7
    NOTE[(5, 1)] = 23                          # SW24: track key 8
    for r in range(4):                         # ENC1-ENC8 pushes: rows 0-3, columns 4-5
        NOTE[(r, 4)] = 32 + 2 * r
        NOTE[(r, 5)] = 33 + 2 * r
    NOTE[(5, 2)] = 40                          # ENC9 push
    # On the board, the knob labelled ENC11 sits between ENC9 and ENC10, so these two are
    # numbered by position instead: the 10th knob from the left sends 10, the last one 11.
    NOTE[(5, 3)] = 42                          # ENC10 on the board (last knob) push
    NOTE[(5, 4)] = 41                          # ENC11 on the board (10th knob) push
else:
    for r in range(6):
        NOTE[(r, 4)] = 32 + r                  # knob pushes 1-6: column 4
        NOTE[(r, 6)] = 48 + r                  # steps 1-6: column 6
        NOTE[(r, 7)] = 54 + r                  # steps 7-12: column 7
        NOTE[(r, 9)] = 16 + r                  # track keys 1-6: column 9
        NOTE[(r, 10)] = 24 + r                 # new keys 1-6: column 10
    for r in range(5):
        NOTE[(r, 5)] = 38 + r                  # knob pushes 7-11: column 5
    for r in range(4):
        NOTE[(r, 8)] = 60 + r                  # steps 13-16: column 8
    NOTE[(4, 8)] = 22                          # track key 7
    NOTE[(5, 8)] = 23                          # track key 8

# ---------------------------------------------------------------- pin check
# Instead of acting as a controller, report every knob wire (GP14-GP35) as it changes, as MIDI CC on
# channel 14: CC number = wire (0 = GP14 ... 21 = GP35), value 127 = high, 0 = low; plus all of them
# every half second. The Pi's test screen (test-controls.sh) shows them.
# Start it from the test screen (P sends CC 127 = 127 on channel 14), or hold SW1 while plugging in.
# P again (CC 127 = 0) restarts the board as a normal controller.
PIN_CHECK_ON = bytes((0xB0 | 13, 127, 127))
PIN_CHECK_OFF = bytes((0xB0 | 13, 127, 0))


def heard(message):
    """True if the Pi just sent this MIDI message."""
    try:
        data = usb_midi.ports[0].read(64)
    except Exception:
        return False
    return bool(data) and message in data


def pin_check():
    import digitalio
    out = usb_midi.ports[1]
    wires = []
    for n in range(14, 36):
        w = digitalio.DigitalInOut(pin(n))
        w.switch_to_input(pull=digitalio.Pull.UP)
        wires.append(w)
    last = [None] * len(wires)
    every = 0.0
    print("Pin check: turn each knob slowly; unplug to stop")
    while True:
        now = time.monotonic()
        full = now - every > 0.5
        for i, w in enumerate(wires):
            v = w.value
            if v != last[i] or full:
                last[i] = v
                try:
                    out.write(bytes((0xB0 | 13, i, 127 if v else 0)))
                except Exception:
                    pass
        if full:
            every = now
            if heard(PIN_CHECK_OFF):
                microcontroller.reset()        # start again as a normal controller
        time.sleep(0.0005)


time.sleep(2.0)                                # let the matrix scan; time to hold SW1 after plugging in
_event = keypad.Event()
_held = False
while matrix.events.get_into(_event):
    if _event.pressed and _event.key_number == 0:
        _held = True
if _held:
    pin_check()                                # never returns

# ---------------------------------------------------------------- knobs (A/B on GP14/15 ... GP34/35)


class PolledEncoder:
    """Used only if the chip runs out of hardware encoder readers."""
    TABLE = (0, -1, 1, 0, 1, 0, 0, -1, -1, 0, 0, 1, 0, 1, -1, 0)

    def __init__(self, a, b):
        import digitalio
        self.a = digitalio.DigitalInOut(a)
        self.b = digitalio.DigitalInOut(b)
        for p in (self.a, self.b):
            p.switch_to_input(pull=digitalio.Pull.UP)
        self.state = (self.a.value << 1) | self.b.value
        self.steps = 0
        self.position = 0

    def poll(self):
        s = (self.a.value << 1) | self.b.value
        self.steps += self.TABLE[(self.state << 2) | s]
        self.state = s
        while self.steps >= DIVISOR:
            self.steps -= DIVISOR
            self.position += 1
        while self.steps <= -DIVISOR:
            self.steps += DIVISOR
            self.position -= 1


encoders = []
polled = []
for e in range(11):
    a, b = pin(14 + 2 * e), pin(15 + 2 * e)
    try:
        import rotaryio
        enc = rotaryio.IncrementalEncoder(a, b, divisor=DIVISOR)
    except Exception:
        enc = PolledEncoder(a, b)
        polled.append(enc)
    encoders.append(enc)
last = [enc.position for enc in encoders]
# by position; on the v0.1 board, ENC10 is the last knob and ENC11 the 10th. The v0.2 knob board is wired in order.
KNOB_CC = [1, 2, 3, 4, 5, 6, 7, 8, 9, 11, 10] if BOARD == 1 else list(range(1, 12))
if polled:
    print("%d knobs read by polling" % len(polled))

# ---------------------------------------------------------------- send

midi = usb_midi.ports[1]


def send(*data):
    try:
        midi.write(bytes(data))
    except Exception:
        pass                                   # not connected to a host yet


print("Console controls ready")
event = keypad.Event()
check_at = 0.0
while True:
    now = time.monotonic()
    if now >= check_at:                        # the test screen asking for the pin check
        check_at = now + 0.2
        if heard(PIN_CHECK_ON):
            for enc in encoders:
                enc.deinit() if hasattr(enc, "deinit") else (enc.a.deinit(), enc.b.deinit())
            pin_check()
    for enc in polled:
        enc.poll()
    while matrix.events.get_into(event):
        row, col = divmod(event.key_number, len(COL_PINS))
        note = NOTE.get((row, col))
        if note is None:
            continue
        if event.pressed:
            send(0x90 | CHANNEL, note, 127)
        else:
            send(0x80 | CHANNEL, note, 0)
    for i, enc in enumerate(encoders):
        pos = enc.position
        delta = pos - last[i]
        if delta:
            last[i] = pos
            send(0xB0 | CHANNEL, KNOB_CC[i], max(1, min(127, 64 + delta)))
    if not polled:
        time.sleep(0.001)
